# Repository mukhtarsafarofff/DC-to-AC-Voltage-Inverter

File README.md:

(ENG)  This Power Inverter is a backup power supply using a 12V battery that will invert it to 220V AC. Using this Power Inverter we can use your appliances like TV, Radio, Audio system as well as lightings like a bulb, fluorescent, etc. This inverter has three main parts: 12V Battery, Inverter Board, and Centertapped Transformer. This inverter has a Tl494 PWM IC that provides a pulse with modulation, the two output pins of this PWM ic are responsible for ON state and OFF state of the power mosfet. Power Mosfet (IRFZ44N) i is a specific type of metal–oxide–semiconductor field-effect transistor designed to handle significant power levels. The drain terminal of the MOSFET is connected to the center-tapped of the transformer, the power MOSFET is ON and OFF synchronize to the PWM IC output pin, and the Centertapped transformer are in STEP UP condition (from 12V DC to 22OV AC). The power of inverter are dependent to the power capacity of the battery and transformer. This inverter has Reverse polarity protection, wherein if you connected the battery in the WRONG WAY the inverter is safe, because of this 1N4148 (1A). 1N4148 diode has a lower voltage drop compared to the other diode. Therefore the power losses are significantly lower compared to other diodes. This inverter is in the square waveform, therefore you can only use it in resistive load like a bulb, and also you can use it and an electronic device like TV's.

(DEU)  Dieser Power Inverter ist eine Notstromversorgung, die eine 12V Batterie verwendet und diese in 220V AC umwandelt. Mit diesem Power Inverter können Sie Ihre Geräte wie Fernseher, Radio, Audiosystem sowie Beleuchtungen wie Glühbirnen,Leuchtstofflampen usw. nutzen.  Der Inverter besteht aus drei Hauptteilen: 12V Batterie, Inverterplatine und mittelanzapfender Transformator.  Dieser Inverter verfügt über einen TL494 PWM IC, der eine Pulsweitenmodulation bereitstellt. Die zwei Ausgangspins dieses PWM ICs steuern den ON- und OFF-Zustand des Power-Mosfets. Der Power Mosfet (IRFZ44N) ist eine spezielle Art von Metalloxid-Halbleiter-Feldeffekttransistor, der für hohe Leistungsniveaus ausgelegt ist. Das Drain-Terminal des MOSFET ist mit der Mittelanzapfung des Transformators verbunden, der Power MOSFET schaltet synchron zu den Ausgangspins des PWM IC ein und aus, und der mittelanzapfende Transformator befindet sich im STEP-UP-Zustand (von 12V DC zu 220V AC). Die Leistung des Inverters hängt von der Kapazität der Batterie und des Transformators ab. Dieser Inverter hat einen Verpolungsschutz, wodurch er sicher bleibt, wenn Sie die Batterie falsch anschließen, dank der Diode 1N4148 (1A), die einen geringeren Spannungsabfall im Vergleich zu anderen Dioden aufweist. Daher sind die Leistungsverluste im Vergleich zu anderen Dioden deutlich geringer. Dieser Inverter erzeugt eine quadratische Wellenform und ist daher nur für ohmsche Lasten wie Glühbirnen oder auch für elektronische Geräte wie Fernseher geeignet.

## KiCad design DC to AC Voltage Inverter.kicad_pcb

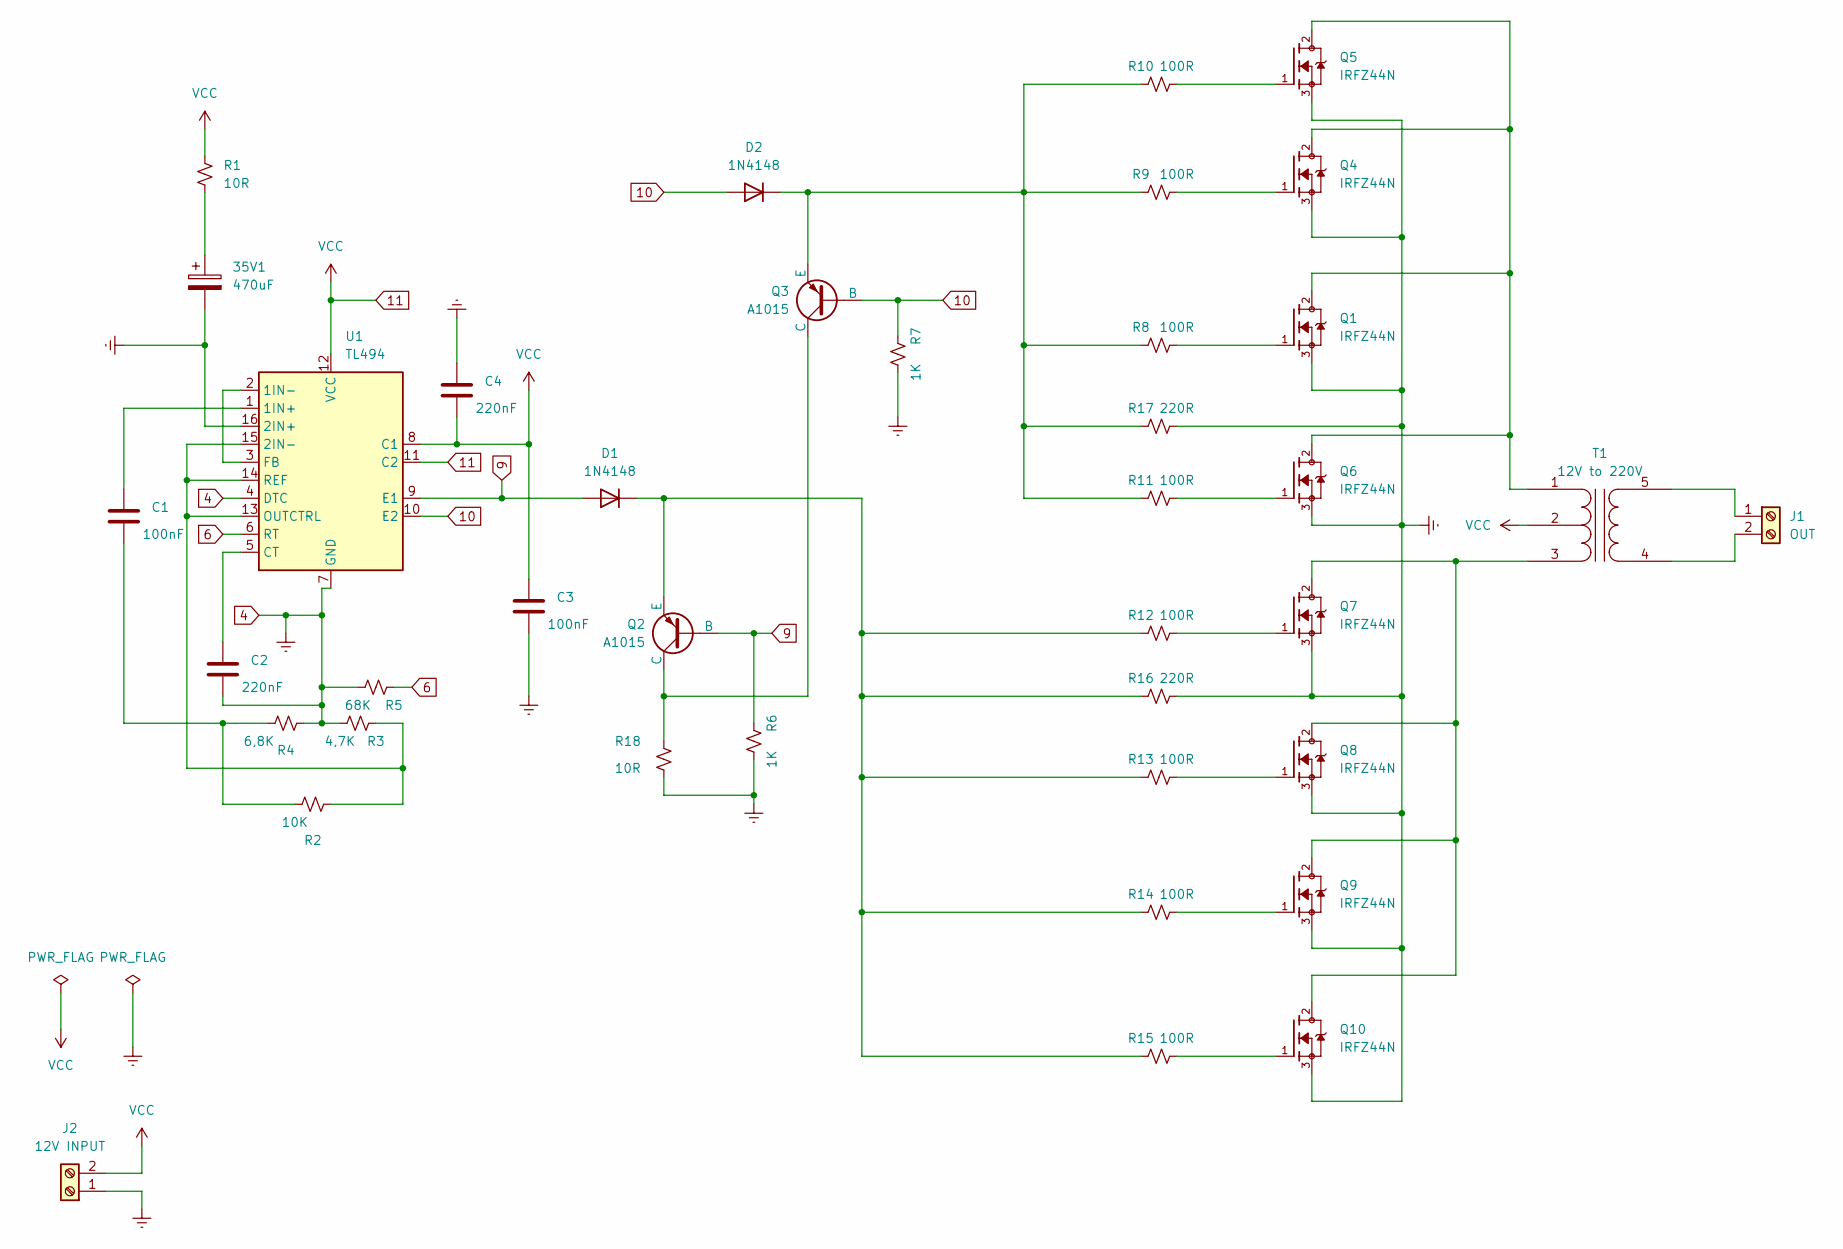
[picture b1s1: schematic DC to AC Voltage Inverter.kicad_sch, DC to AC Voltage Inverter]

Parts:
35V1: 470uF; CP_Radial_D10.0mm_P7.50mm
C1, C3: 100nF; C_Disc_D7.5mm_W5.0mm_P7.50mm
C2, C4: 220nF; C_Disc_D7.5mm_W5.0mm_P7.50mm
D1, D2: 1N4148; D_DO-35_SOD27_P7.62mm_Horizontal
J1: OUT; TerminalBlock_bornier-2_P5.08mm
J2: 12V INPUT; TerminalBlock_bornier-2_P5.08mm
Q1, Q4, Q5, Q6, Q7, Q8, Q9, Q10: IRFZ44N; TO254P1016X419X2286-3; PARTREV 09/21/10
Q2, Q3: A1015; TO254P1016X419X2286-3
R1, R18: 10R; R_Axial_DIN0516_L15.5mm_D5.0mm_P25.40mm_Horizontal
R2: 10K; R_Axial_DIN0516_L15.5mm_D5.0mm_P25.40mm_Horizontal
R3: 4,7K; R_Axial_DIN0516_L15.5mm_D5.0mm_P25.40mm_Horizontal
R4: 6,8K; R_Axial_DIN0516_L15.5mm_D5.0mm_P25.40mm_Horizontal
R5: 68K; R_Axial_DIN0516_L15.5mm_D5.0mm_P25.40mm_Horizontal
R6, R7: 1K; R_Axial_DIN0516_L15.5mm_D5.0mm_P25.40mm_Horizontal
R8, R9, R10, R11, R12, R13, R14, R15: 100R; R_Axial_DIN0516_L15.5mm_D5.0mm_P25.40mm_Horizontal
R16, R17: 220R; R_Axial_DIN0516_L15.5mm_D5.0mm_P25.40mm_Horizontal
T1: 12V to 220V; Transformer_Toroid_Horizontal_D18.0mm
U1: TL494; DIP-16_W7.62mm

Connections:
4: 35V1.2, C2.2, C3.2, C4.1, J2.1, Q1.3, Q4.3, Q5.3, Q6.3, Q7.3, Q8.3, Q9.3, Q10.3, R3.1, R4.2, R5.1, R6.1, R7.1, R16.1, R17.1, R18.1, U1.4 (DTC), U1.7 (GND), U1.16 (2IN+)
6: R5.2, U1.6 (RT)
9: D1.2 (A), Q2.2 (B), R6.2, U1.9 (E1)
10: D2.2 (A), Q3.2 (B), R7.2, U1.10 (E2)
11: C3.1, C4.2, J2.2, R1.1, T1.2 (PM), U1.8 (C1), U1.11 (C2), U1.12 (VCC)
unnamed: 35V1.1, R1.2
unnamed: C1.2, R2.1, R4.1
unnamed: D1.1 (K), Q2.3 (E), R12.2, R13.2, R14.2, R15.2, R16.2
unnamed: D2.1 (K), Q3.3 (E), R8.2, R9.2, R10.2, R11.2, R17.2
unnamed: J1.1, T1.5 (S2)
unnamed: J1.2, T1.4 (S1)
unnamed: Q1.1, R8.1
unnamed: Q2.1 (C), Q3.1 (C), R18.2
unnamed: Q4.1, R9.1
unnamed: Q5.1, R10.1
unnamed: Q6.1, R11.1
unnamed: Q7.1, R12.1
unnamed: Q8.1, R13.1
unnamed: Q9.1, R14.1
unnamed: Q10.1, R15.1
unnamed: Q1.2, Q4.2, Q5.2, Q6.2, T1.1 (PR1)
unnamed: Q7.2, Q8.2, Q9.2, Q10.2, T1.3 (PR2)
unnamed: C1.1, U1.1 (1IN+)
unnamed: U1.2 (1IN-), U1.3 (FB)
unnamed: R2.2, R3.2, U1.13 (OUTCTRL), U1.14 (REF), U1.15 (2IN-)
unnamed: C2.1, U1.5 (CT)

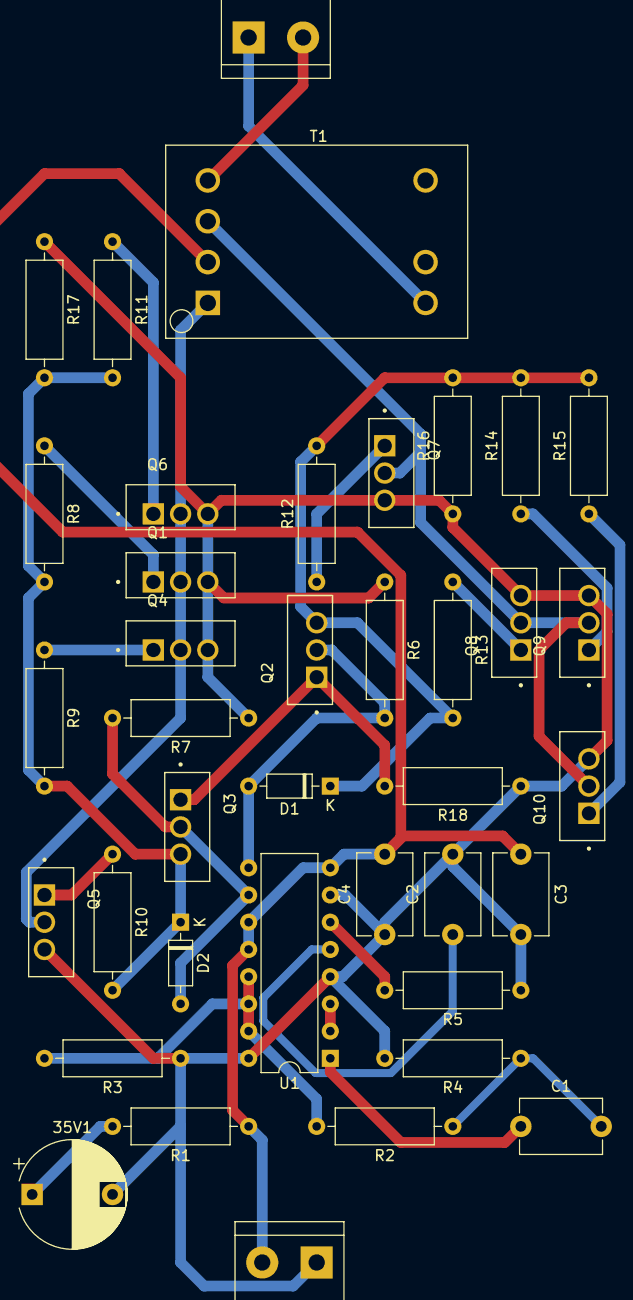
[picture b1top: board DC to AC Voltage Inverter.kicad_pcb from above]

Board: 2 copper layers, 39 parts (0 on the bottom side), 26 nets.

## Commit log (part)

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2024-03-27 DC to AC Voltage Inverter is accomplished
